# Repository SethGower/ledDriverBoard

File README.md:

# LED Driver Board

This is a Circuit and PCB design for an LED Strip driver I designed for personal use. I designed this to be able to have an LED strip on the perimeter of my bedroom. Given the perimeter is about 55 feet, this would require a lot of power. The original strip I looked at required 24W/m at full brightness of all 4 color channels (RGBW), since this was 60 LED/m. Due to the power requirements of this, I reduced the strip I was using to a 30 LED/m, which required 9.6 W/m. I originally designed it to drive an LED strip that doesn't have individual addressable channels. I changed the design to be able to drive an individually addressable strip, in order to have more control over the lighting.

There are three designs in this repo. The original, located in `Non_Addressable` contains the original design, which used the non addressable LED strip. The intention with this design was to use [ESPHome](https://esphome.io). The different channels were to be driven with PWM to control brightness. The Second design, for the addressable LED strips is located in `Addressable_Driver`. This was intended to be used with [WLED](https://kno.wled.ge). The final design, located in `Unified` is a combination of the two designs, on the same PCB. So only one design needs to be manufactured, and the user can decide which portion to use. All of the designs use an ESP32-DO-IT board as the controller. Make sure it is the 30 pin version.

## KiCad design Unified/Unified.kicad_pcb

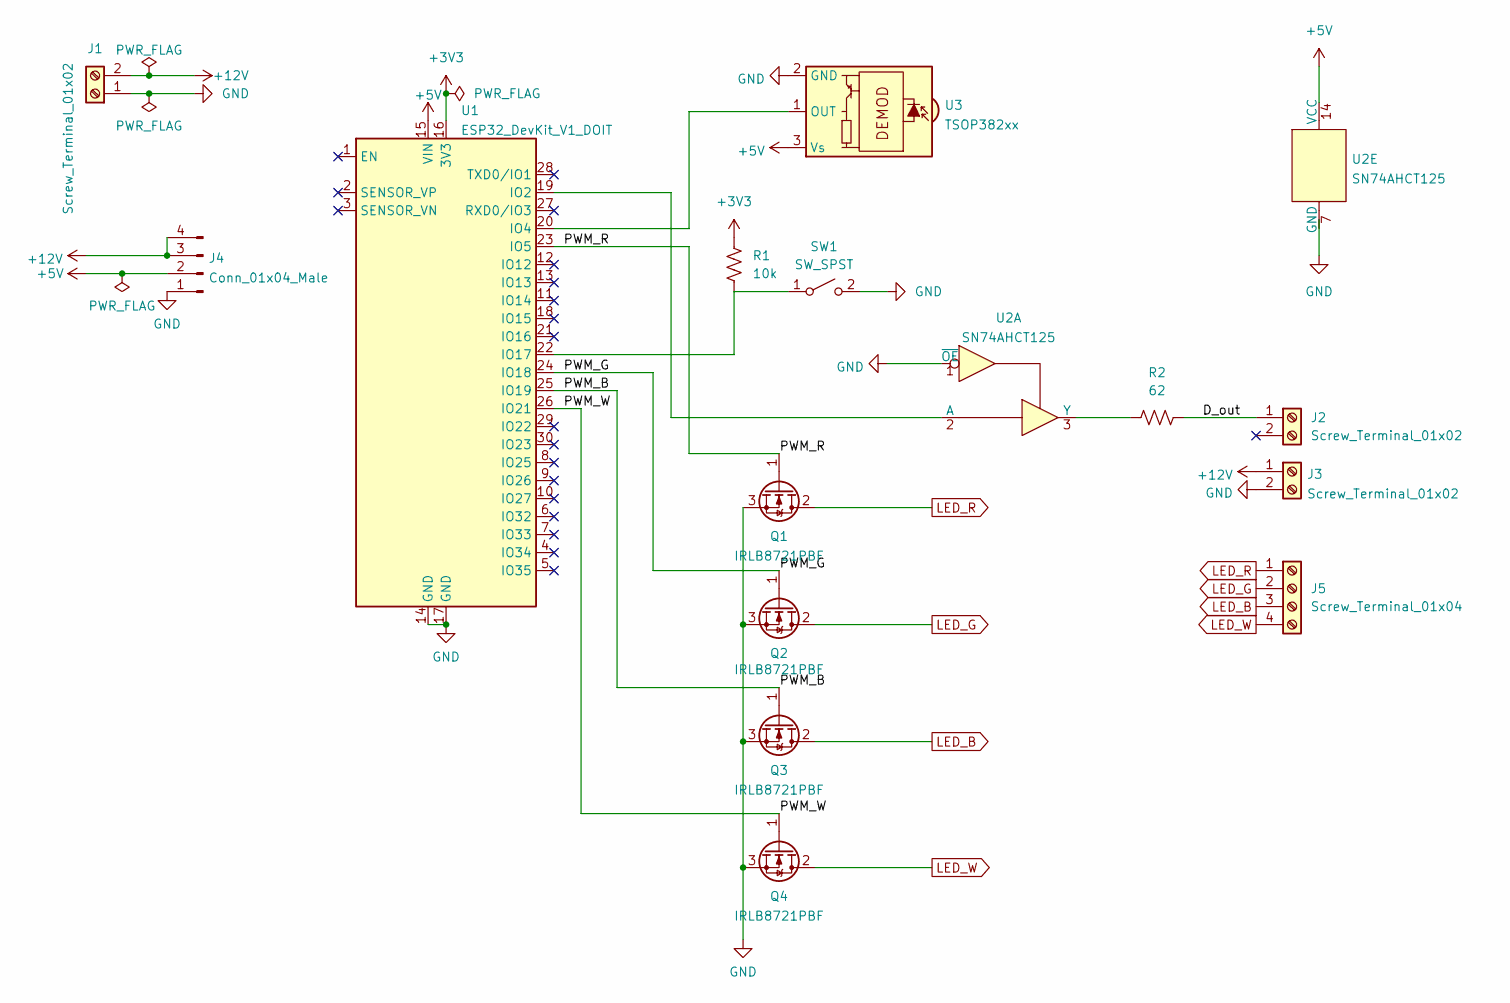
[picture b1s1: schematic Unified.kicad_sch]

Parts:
J1, J3: Screw_Terminal_01x02; TerminalBlock_Dinkle_DT-55-B01X-02_P10.00mm
J2: Screw_Terminal_01x02; TerminalBlock_bornier-2_P5.08mm
J4: Conn_01x04_Male; PinHeader_1x04_P2.54mm_Vertical
J5: Screw_Terminal_01x04; TerminalBlock_bornier-4_P5.08mm
Q1, Q2, Q3, Q4: IRLB8721PBF; TO-220-3_Vertical
R1: 10k; R_Axial_DIN0207_L6.3mm_D2.5mm_P7.62mm_Horizontal
R2: 62; R_Axial_DIN0207_L6.3mm_D2.5mm_P7.62mm_Horizontal
SW1: SW_SPST; SW_PUSH_6mm_H5mm
U1: ESP32_DevKit_V1_DOIT; esp32_devkit_v1_doit
U2: SN74AHCT125; DIP-14_W7.62mm
U3: TSOP382xx; Vishay_MINICAST-3Pin

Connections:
+3V3: R1.1, U1.16 (3V3)
+5V: J4.2, U1.15 (VIN), U2.14 (VCC), U3.3 (Vs)
+12V: J1.2, J3.1, J4.3, J4.4; also elsewhere on the board
/D_out: J2.1, R2.2
/PWM_B: Q3.1 (G), U1.25 (IO19)
/PWM_G: Q2.1 (G), U1.24 (IO18)
/PWM_R: Q1.1 (G), U1.23 (IO5)
/PWM_W: Q4.1 (G), U1.26 (IO21)
GND: J1.1, J3.2, J4.1, Q1.3 (S), Q2.3 (S), Q3.3 (S), Q4.3 (S), SW1.2 (B), U1.14 (GND), U1.17 (GND), U2.1 (~OE), U3.2 (GND); also elsewhere on the board
LED_B: J5.3, Q3.2 (D)
LED_G: J5.2, Q2.2 (D)
LED_R: J5.1, Q1.2 (D)
LED_W: J5.4, Q4.2 (D)
unnamed: R1.2, SW1.1 (A), U1.22 (IO17)
unnamed: R2.1, U2.3 (Y)
unnamed: U1.19 (IO2), U2.2 (A)
unnamed: U1.20 (IO4), U3.1 (OUT)

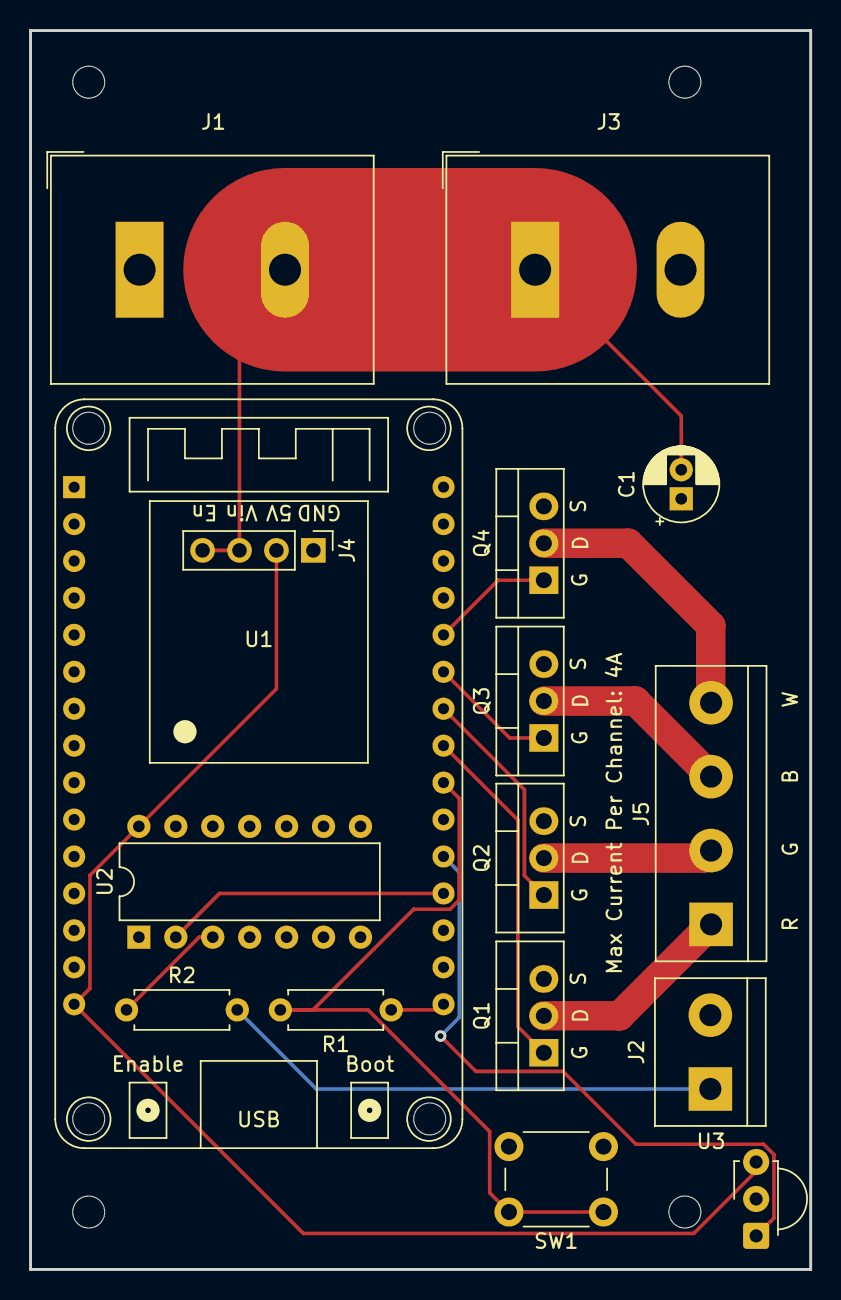
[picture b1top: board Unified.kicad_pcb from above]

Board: 2 copper layers, 53.6 x 85.2 mm, 16 parts (0 on the bottom side), 17 nets.

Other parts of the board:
C1: 1000uF; CP_Radial_D5.0mm_P2.00mm

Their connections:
+12V: C1.2; also elsewhere on the board
GND: C1.1; also elsewhere on the board

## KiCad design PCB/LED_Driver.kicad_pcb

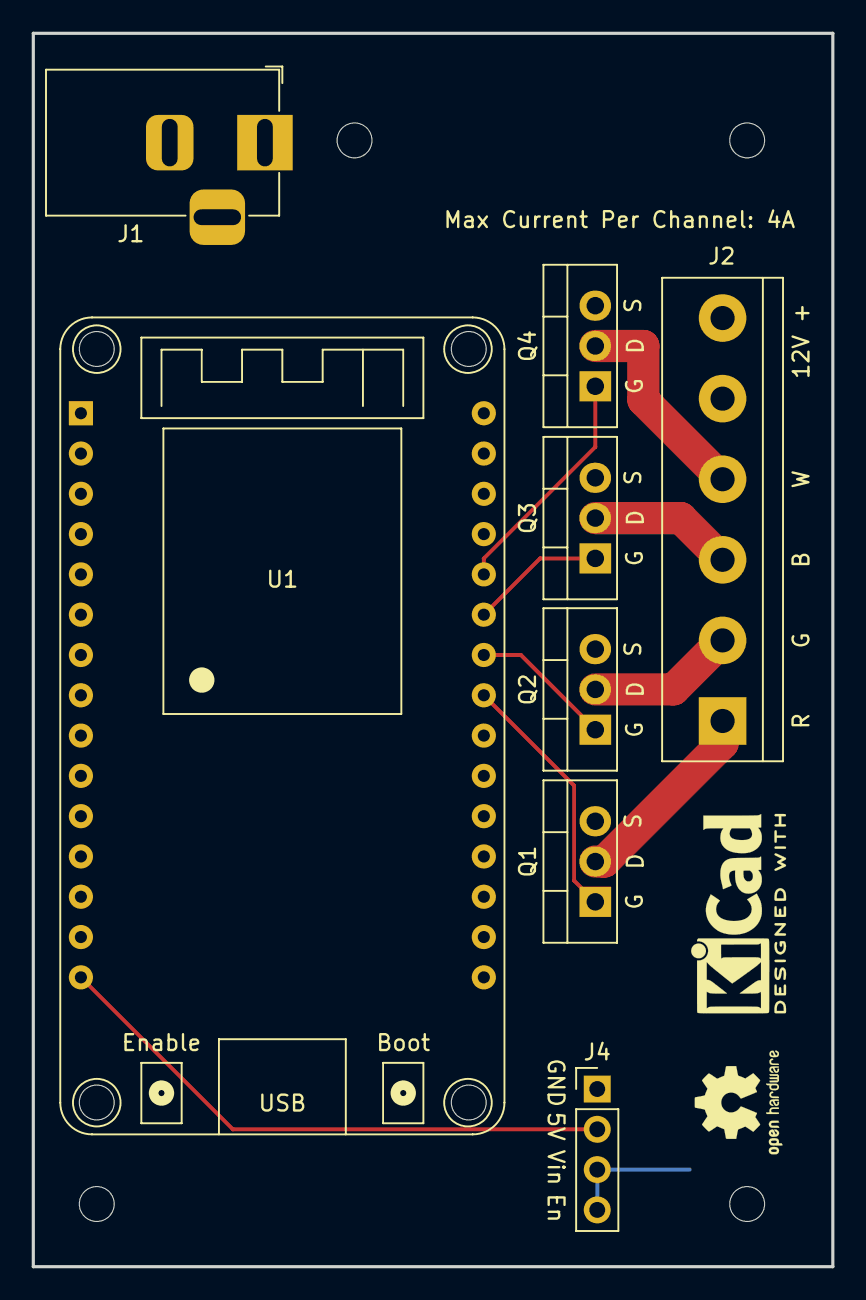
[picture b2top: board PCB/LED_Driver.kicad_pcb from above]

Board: 2 copper layers, 50.4 x 77.8 mm, 8 parts (0 on the bottom side), 11 nets.

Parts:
J1: Conn_Coaxial_Power; BarrelJack_Horizontal
J2: Screw_Terminal_01x06; TerminalBlock_bornier-6_P5.08mm
J4: Conn_01x04_Male; PinHeader_1x04_P2.54mm_Vertical
Q1, Q2, Q3, Q4: IRLB8721PBF; TO-220-3_Vertical
U1: ESP32_DevKit_V1_DOIT; esp32_devkit_v1_doit

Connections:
+5V: J4.2, U1.15 (VIN)
+12V: J1.1 (In), J2.5, J2.6, J4.3, J4.4
/PWM_B: Q3.1 (G), U1.25 (IO19)
/PWM_G: Q2.1 (G), U1.24 (IO18)
/PWM_R: Q1.1 (G), U1.23 (IO5)
/PWM_W: Q4.1 (G), U1.26 (IO21)
GND: J1.2 (Ext), J4.1, Q1.3 (S), Q2.3 (S), Q3.3 (S), Q4.3 (S), U1.14 (GND), U1.17 (GND)
LED_B: J2.3, Q3.2 (D)
LED_G: J2.2, Q2.2 (D)
LED_R: J2.1, Q1.2 (D)
LED_W: J2.4, Q4.2 (D)

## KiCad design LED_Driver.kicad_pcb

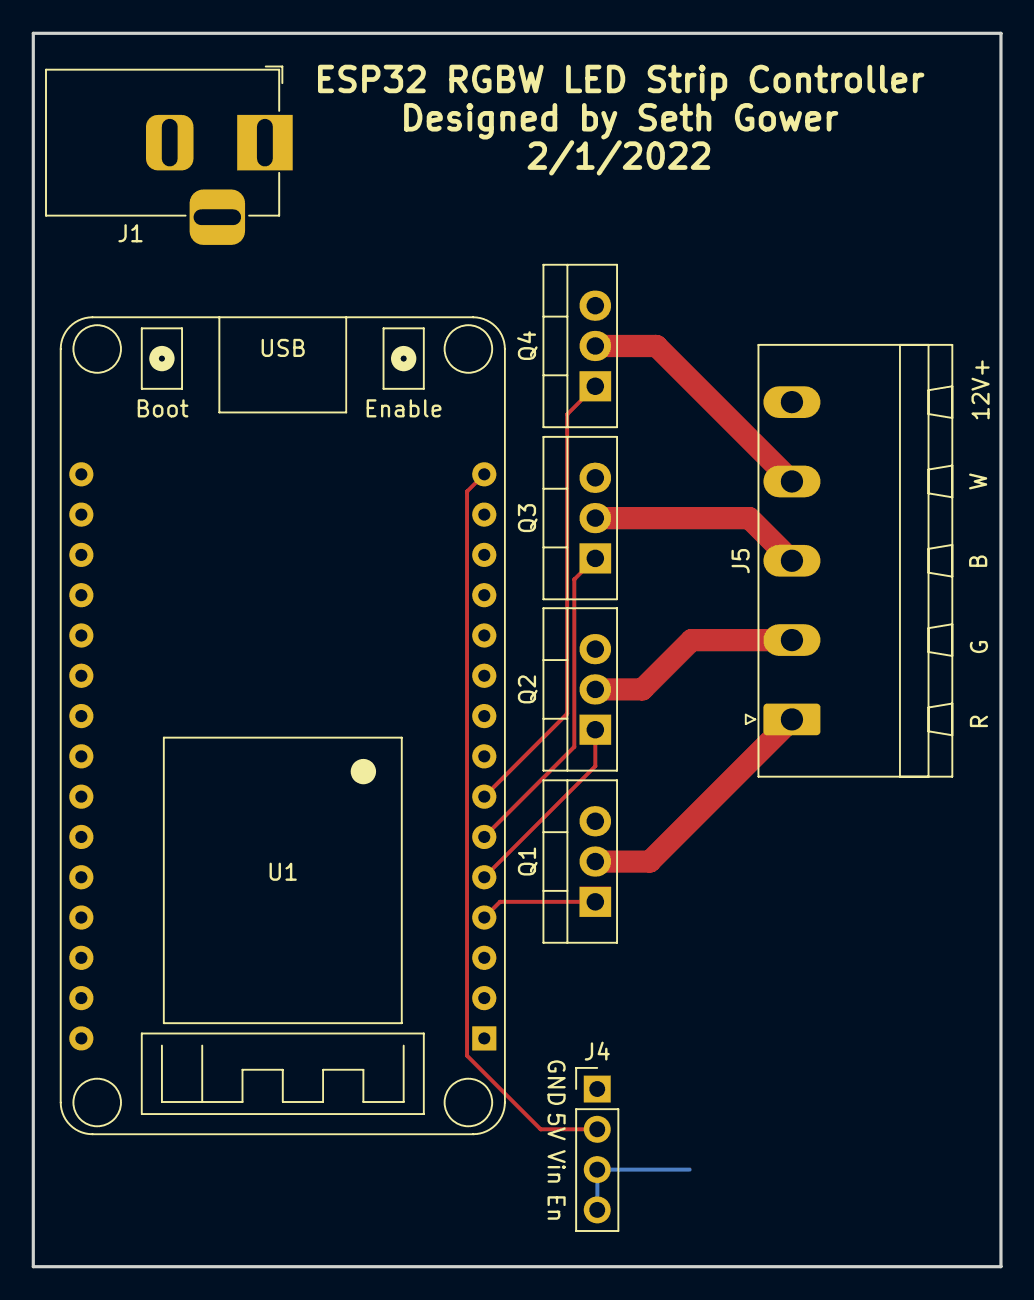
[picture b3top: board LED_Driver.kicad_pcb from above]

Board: 2 copper layers, 61.0 x 77.8 mm, 8 parts (0 on the bottom side), 11 nets.

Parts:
J1: Conn_Coaxial_Power; BarrelJack_Horizontal
J4: Conn_01x04_Male; PinHeader_1x04_P2.54mm_Vertical
J5: Screw_Terminal_01x05; PhoenixContact_MSTBA_2,5_5-G_1x05_P5.00mm_Horizontal
Q1, Q2, Q3, Q4: IRLB8721PBF; TO-220-3_Vertical
U1: ESP32_DevKit_V1_DOIT; esp32_devkit_v1_doit

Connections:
+5V: J4.2, U1.15 (VIN)
+12V: J1.1 (In), J4.3, J4.4, J5.5
/PWM_B: Q3.1 (G), U1.6 (IO32)
/PWM_G: Q2.1 (G), U1.5 (IO35)
/PWM_R: Q1.1 (G), U1.4 (IO34)
/PWM_W: Q4.1 (G), U1.7 (IO33)
GND: J1.2 (Ext), J4.1, Q1.3 (S), Q2.3 (S), Q3.3 (S), Q4.3 (S), U1.14 (GND), U1.17 (GND)
LED_B: J5.3, Q3.2 (D)
LED_G: J5.2, Q2.2 (D)
LED_R: J5.1, Q1.2 (D)
LED_W: J5.4, Q4.2 (D)

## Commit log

2022-02-01 v0.1: Initial Commit
2022-02-02 Moves PCB files into subdirectory
2022-02-02 adds gitignore
2022-02-03 minor updates
2022-02-03 Updates the connections to the ESP32. The original pins were input only pins, according to esphome
2022-02-05 Makes board smaller using proper terminal blocks
2022-02-05 Updates pins that are driving gates of transistors. 3 of the original ones were strapping pins on the esp32
2022-02-05 Moves the original design to different directory. Working on addressable version
2022-02-05 Adds design for addressable driver board
2022-02-06 Adds resistor for data output for addressable version
2022-02-06 Finishes addressable driver
2022-02-06 Moves original design
2022-02-06 Adds Unified Design. With both addressable and non addressable
2022-02-06 adds main readme
2022-02-07 Adds ESP32 footprint stuff as a local library, instead of global
2022-02-07 Moves the submodule so I can add my own custom libraries.
2022-02-07 removes info cache
2022-02-07 Removes 12V and Ground outputs to LED strip. This will be done with thicker wire outside of PCB, due to high trace width requirements
2022-02-09 Adds custom symbol for the level shifter
